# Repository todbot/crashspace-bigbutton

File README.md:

# crashspace-bigbutton

Firmware and schematics for the [CrashSpace](https://blog.crashspace.org/)
"BigButton" hardware interface to https://crashspacela.com/sign/

At [CrashSpace](https://blog.crashspace.org/) we have a publicly-viewable
"sign" at https://crashspacela.com/sign/ to let members know when the
space is open. This sign page is updated by a big button in the front
room.  Press it, the sign webpage updates, and you've promised to be
in the space for an hour.

This repo is documentation of the new BigButton hardware that was installed
at CrashSpace in Jan 2017.

## Table of Contents

* [Functionality](#functionality)
* [In use](#in-use)
* [Implementation](#implementation)
 * [Implementation - Hardware](#implementation---hardware)
    * [Converting 3v3 ESP8266 output for WS2812 / Neopixel  LEDs](#converting-3v3-esp8266-output-for-ws2812--neopixel--leds)
    * [Othermill design considerations](#othermill-design-considerations)
 * [Implementation - Firmware](#implementation---firmware)
    * [ArduinoJson is awesome](#arduinojson-is-awesome)
    * [CrashSpace sign server JSON API](#crashspace-sign-server-json-api)

## Functionality

* The BigButton consists of a pushbutton and a ring of LEDs
* The user pushes the button to signify they're at the space
* The LED ring displays whether or not CrashSpace is "open" or "closed"
* The LED ring visually shows a count down from 60 minutes,
  giving a rough indication of time left
* Pushing the button sends an HTTP request to the CrashSpace "sign" server
   at https://crashspacela.com/sign/
* (new!) The button periodically fetches a JSON feed from the
  sign server, getting time left and whether space is open or not.
  This allows for multiple buttons.

## In use

  * Button is pulsing ORANGE: CrashSpace is closed
  * Push Button.  Button spins a RAINBOW for a second or two, then
  * Button is pulsing TEAL: CrashSpace is open
  * Button counts down my extinguishing TEAL LEDs in an arc
  * Button flashing RED: Internet is down

## Implementation

The original BigButton implementation was an Arduino Uno with WS2812 LEDs inside a
large taplight tied to a Linux netbook for WiFi connectivity.
An upgrade button created several years late used an early version of the
Particle Photon Internet Button kit in a custom 3d printed enclosure.

This version of BigButton uses an
[ESP82166 Wemos D1 mini](https://www.wemos.cc/product/d1-mini.html)
WiFi board mounted to a custom carrier board containing 12 WS2812 LEDs.
It uses the [ESP8266 Arduino core](https://github.com/esp8266/Arduino/)
to run an Arduino sketch.

### Implementation - Hardware

The hardware implementation is pretty straight forward.
The Wemos D1 mini ESP8266 board does all the work.
The input is a single button and the output is a string of WS2812 LEDs.

The schematic and layout for the carrier board is:

Eagle format versions of these are in the [schematic](./schematic) folder.

#### Converting 3v3 ESP8266 output for WS2812 / Neopixel  LEDs

One interesting thing about the schematic how the ESP8266 (a 3v3 device)
manages to control 5V WS2812/Neopixel LEDs.  Some WS2812s can be driven by 3v3 logic HIGH, but it's iffy.  The standard solution is a level-shifter buffer to convert 3v3 HIGH to 5V HIGH.

The technique used on this board, however, is to create a "sacrificial" LED that powered not by 5V but by a stepped-down voltage from a standard signal diode
(with its 0.7V voltage drop).  This creates an approx. 4.3V power source that is high enough to drive the LED but brings its concept of logic HIGH (>70% of Vcc) down to what a 3v3 device will output.  Basically, we're building a
special intermediary power supply for a single LED.
The rest of the WS2812 LEDs are driven by 5V.

#### Othermill design considerations

I wanted this board to be millable on an Othermill, so that meant adopting slightly different PCB design techniques.  There are a few reasons for this. For instance, because this board has no soldermask, I want to maximize spacing between copper traces.  Also, I would like to minimize the use of endmills smaller than 1/32" because they are fragile and take a long time to mill.  Thus, the techniques I use are:

* Increase trace width 16 mil (0.016")
* Add ground plane, set its Polygon->Isolate value to 32 mil (0.032")
* Single-sided only design (or minimize back-side traces)
* Space components out to enable easy soldering

The result is below. The Wemos D1 Mini ESP8266 board is mounted on the
backside of the board to minimize its impact on light output.  
The board is mounted on standoffs which are screwed into the modified
taplight. The taplight's switch is reused as the button input.

### Implementation - Firmware

The ESP8266 runs the ["CrashButtonESP"](./CrashButtonESP/) Arduino sketch.

#### ArduinoJson is awesome

The sketch relies on the ArduinoJson library.
With it you can easily parse and use JSON data structures.
And with its magical use of C++ operator-overloading you can have code
like this:

```c++
// jsonstr = '{"is_open":false,"minutes_left":-920.45,"button_presses":[]}'
JsonObject& root = jsonBuffer.parseObject(jsonstr);
bool is_open        = root["is_open"];
double minutes_left = root["minutes_left"];
```

#### CrashSpace sign server JSON API

To enable the button to report real open status
(and not just a dumb countdown), the sign server API at
https://crashspacela.com/sign/
has been updated with a JSON output mode.  There are two versions
of JSON output, picked with the `output` query arg:
* `jsonmin` - "minimal" version with just open status and minutes left
* `json`  - full version that gives a list of recent button presses

The Button uses the minimal one.  Both are shown below:

```json
% curl 'https://crashspacela.com/sign/?output=jsonmin'
{"is_open":false,"minutes_left":-920.45,"button_presses":[]}
```

```json
% curl 'https://crashspacela.com/sign/?output=json'
{
    "is_open": false,
    "minutes_left": -919.43333333333,
    "button_presses": [
        {
            "type": "update",
            "id": "crashbutton1",
            "msg": "Someone is at the space!",
            "diff_mins_max": 60,
            "description": "crashbutton1 - update - 60 mins.",
            "date": "Wed, 11 Jan 2017 21:38:03 -0800",
            "date_epoch": "1484199483"
        },
        {
            "type": "update",
            "id": "crashbutton1",
            "msg": "Someone is at the space!",
            "diff_mins_max": 60,
            "description": "crashbutton1 - update - 60 mins.",
            "date": "Wed, 11 Jan 2017 20:00:00 -0800",
            "date_epoch": "1484193600"
        },
        {
            "type": "update",
            "id": "crashbutton1",
            "msg": "Someone is at the space!",
            "diff_mins_max": 60,
            "description": "crashbutton1 - update - 60 mins.",
            "date": "Wed, 11 Jan 2017 19:16:26 -0800",
            "date_epoch": "1484190986"
        }
    ]
}
```

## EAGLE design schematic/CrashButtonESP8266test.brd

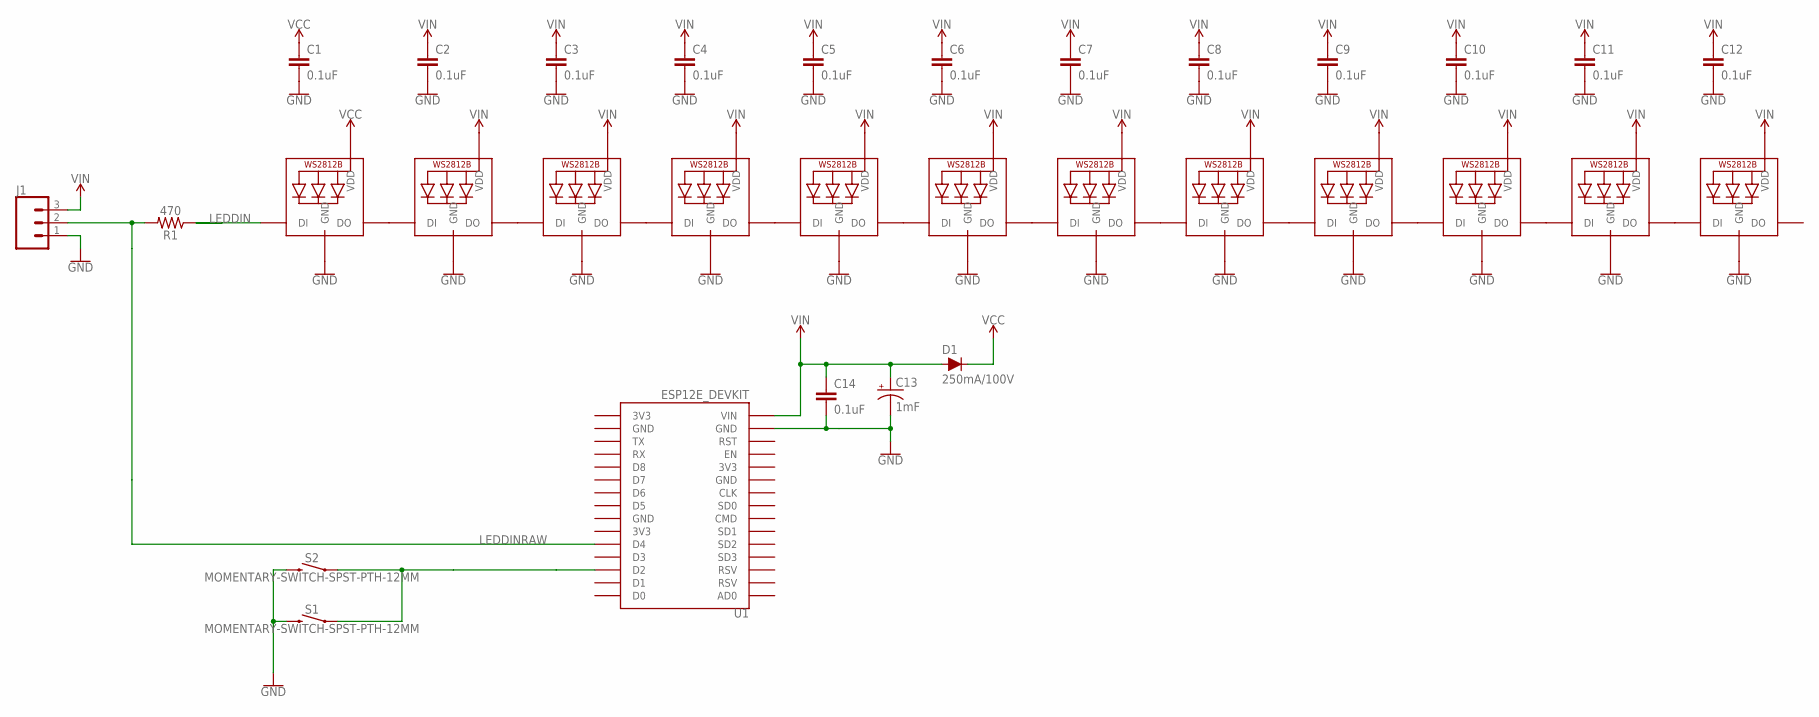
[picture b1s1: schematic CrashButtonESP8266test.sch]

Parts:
C1, C2, C3, C4, C5, C6, C7, C8, C9, C10, C11, C12, C14: 0.1uF; 0603
C13: 1mF; CPOL-RADIAL-5MM-10MM
D1: 250mA/100V; SOD-323
J1: CONN_03; 1X03
LED1, LED2, LED3, LED4, LED5, LED6, LED7, LED8, LED9, LED10, LED11, LED12: WS2812B5050; WS2812B
R1: 470; 0603
S1, S2: MOMENTARY-SWITCH-SPST-PTH-12MM; TACTILE_SWITCH_PTH_12MM
U1: ESP12E_DEVKIT

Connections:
GND: C1.2, C2.2, C3.2, C4.2, C5.2, C6.2, C7.2, C8.2, C9.2, C10.2, C11.2, C12.2, C13.-, C14.2, J1.1, LED1.3-GND (GND), LED2.3-GND (GND), LED3.3-GND (GND), LED4.3-GND (GND), LED5.3-GND (GND), LED6.3-GND (GND), LED7.3-GND (GND), LED8.3-GND (GND), LED9.3-GND (GND), LED10.3-GND (GND), LED11.3-GND (GND), LED12.3-GND (GND), S1.3 (2), S2.3 (2), U1.GND@1 (GND)
LEDDIN: LED1.4-DIN (DI), R1.1
LEDDINRAW: J1.2, R1.2, U1.D4
unnamed: LED1.2-DOUT (DO), LED2.4-DIN (DI)
unnamed: LED2.2-DOUT (DO), LED3.4-DIN (DI)
unnamed: LED3.2-DOUT (DO), LED4.4-DIN (DI)
unnamed: LED4.2-DOUT (DO), LED5.4-DIN (DI)
unnamed: LED5.2-DOUT (DO), LED6.4-DIN (DI)
unnamed: LED6.2-DOUT (DO), LED7.4-DIN (DI)
unnamed: LED8.2-DOUT (DO), LED9.4-DIN (DI)
unnamed: LED9.2-DOUT (DO), LED10.4-DIN (DI)
unnamed: LED10.2-DOUT (DO), LED11.4-DIN (DI)
unnamed: S1.1, S2.1, U1.D2
unnamed: LED7.2-DOUT (DO), LED8.4-DIN (DI)
unnamed: LED11.2-DOUT (DO), LED12.4-DIN (DI)
VCC: C1.1, D1.C, LED1.1-VDD (VDD)
VIN: C2.1, C3.1, C4.1, C5.1, C6.1, C7.1, C8.1, C9.1, C10.1, C11.1, C12.1, C13.+, C14.1, D1.A, J1.3, LED2.1-VDD (VDD), LED3.1-VDD (VDD), LED4.1-VDD (VDD), LED5.1-VDD (VDD), LED6.1-VDD (VDD), LED7.1-VDD (VDD), LED8.1-VDD (VDD), LED9.1-VDD (VDD), LED10.1-VDD (VDD), LED11.1-VDD (VDD), LED12.1-VDD (VDD), U1.VIN

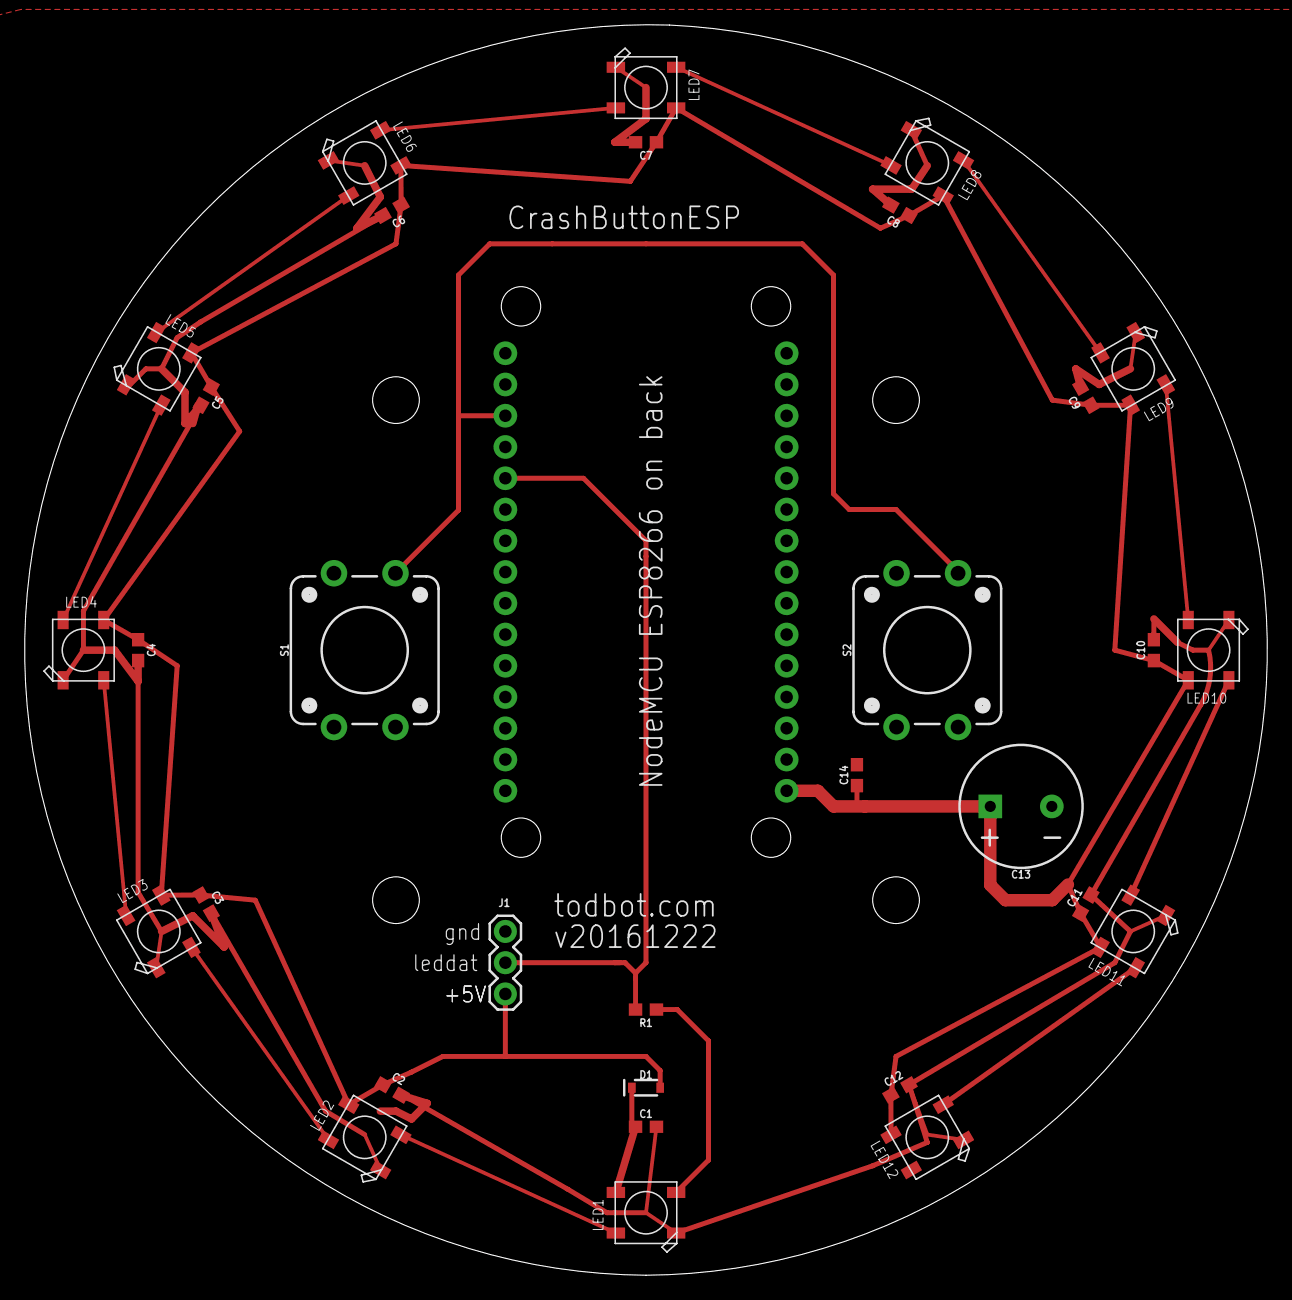
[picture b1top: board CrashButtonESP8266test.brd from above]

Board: 2 copper layers, 101.0 x 101.6 mm, 32 parts (1 on the bottom side), 17 nets.

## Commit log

2016-12-18 super update
2016-12-18 refactor to add ButtonModes
2016-12-19 cleanup
2016-12-19 circular layout
2016-12-20 moved buttoncheck to ledticker, moved ledpin to D4 in case I want to use NeoPixelBus
2016-12-20 made url configurable, added note aboute sacrificial LED
2016-12-20 moved ledticker to end of setup since it seemed to be causing crashes w/ FastLED
2016-12-22 version with enough polygon isolate to be solderable when othermilled
2016-12-23 by default kill old config; show my IP via Serial
2016-12-30 added board that uses D1 mini style esp8266
2016-12-31 small fixes
2017-01-01 added badCount tracking instead of immediately slam to error; also some cleanup
2017-01-02 added button info to API query to help aid future diagnostics
2017-01-04 cleanup diag prints
2017-01-04 schematic updates
2017-01-05 added rainbowTime, also cleanup
2017-01-11 added config file example
2017-01-11 emacs tilde no
2017-01-11 updated schematic
2017-01-12 final tweaks
2017-01-12 fixup construction lines
2017-01-12 started on docs
2017-01-12 more readme updates
2017-01-13 small readme fixes
2017-01-13 added toc
2017-01-15 added sacrificial-neopixel diag
2017-01-23 added platformio.ini for commandline-compile
2017-01-23 added platformio hidden files to gitignore
2017-01-23 added travis
2017-01-23 fix travis
2017-01-23 added build status

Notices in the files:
parts and their libraries:
SparkFun-Switches: Licensing: Creative Commons ShareAlike 4.0 International - https://creativecommons.org/licenses/by-sa/4.0
